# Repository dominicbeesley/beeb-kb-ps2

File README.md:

# beeb-kb-ps2
A BBC Micro Keyboard to PS/2 converter

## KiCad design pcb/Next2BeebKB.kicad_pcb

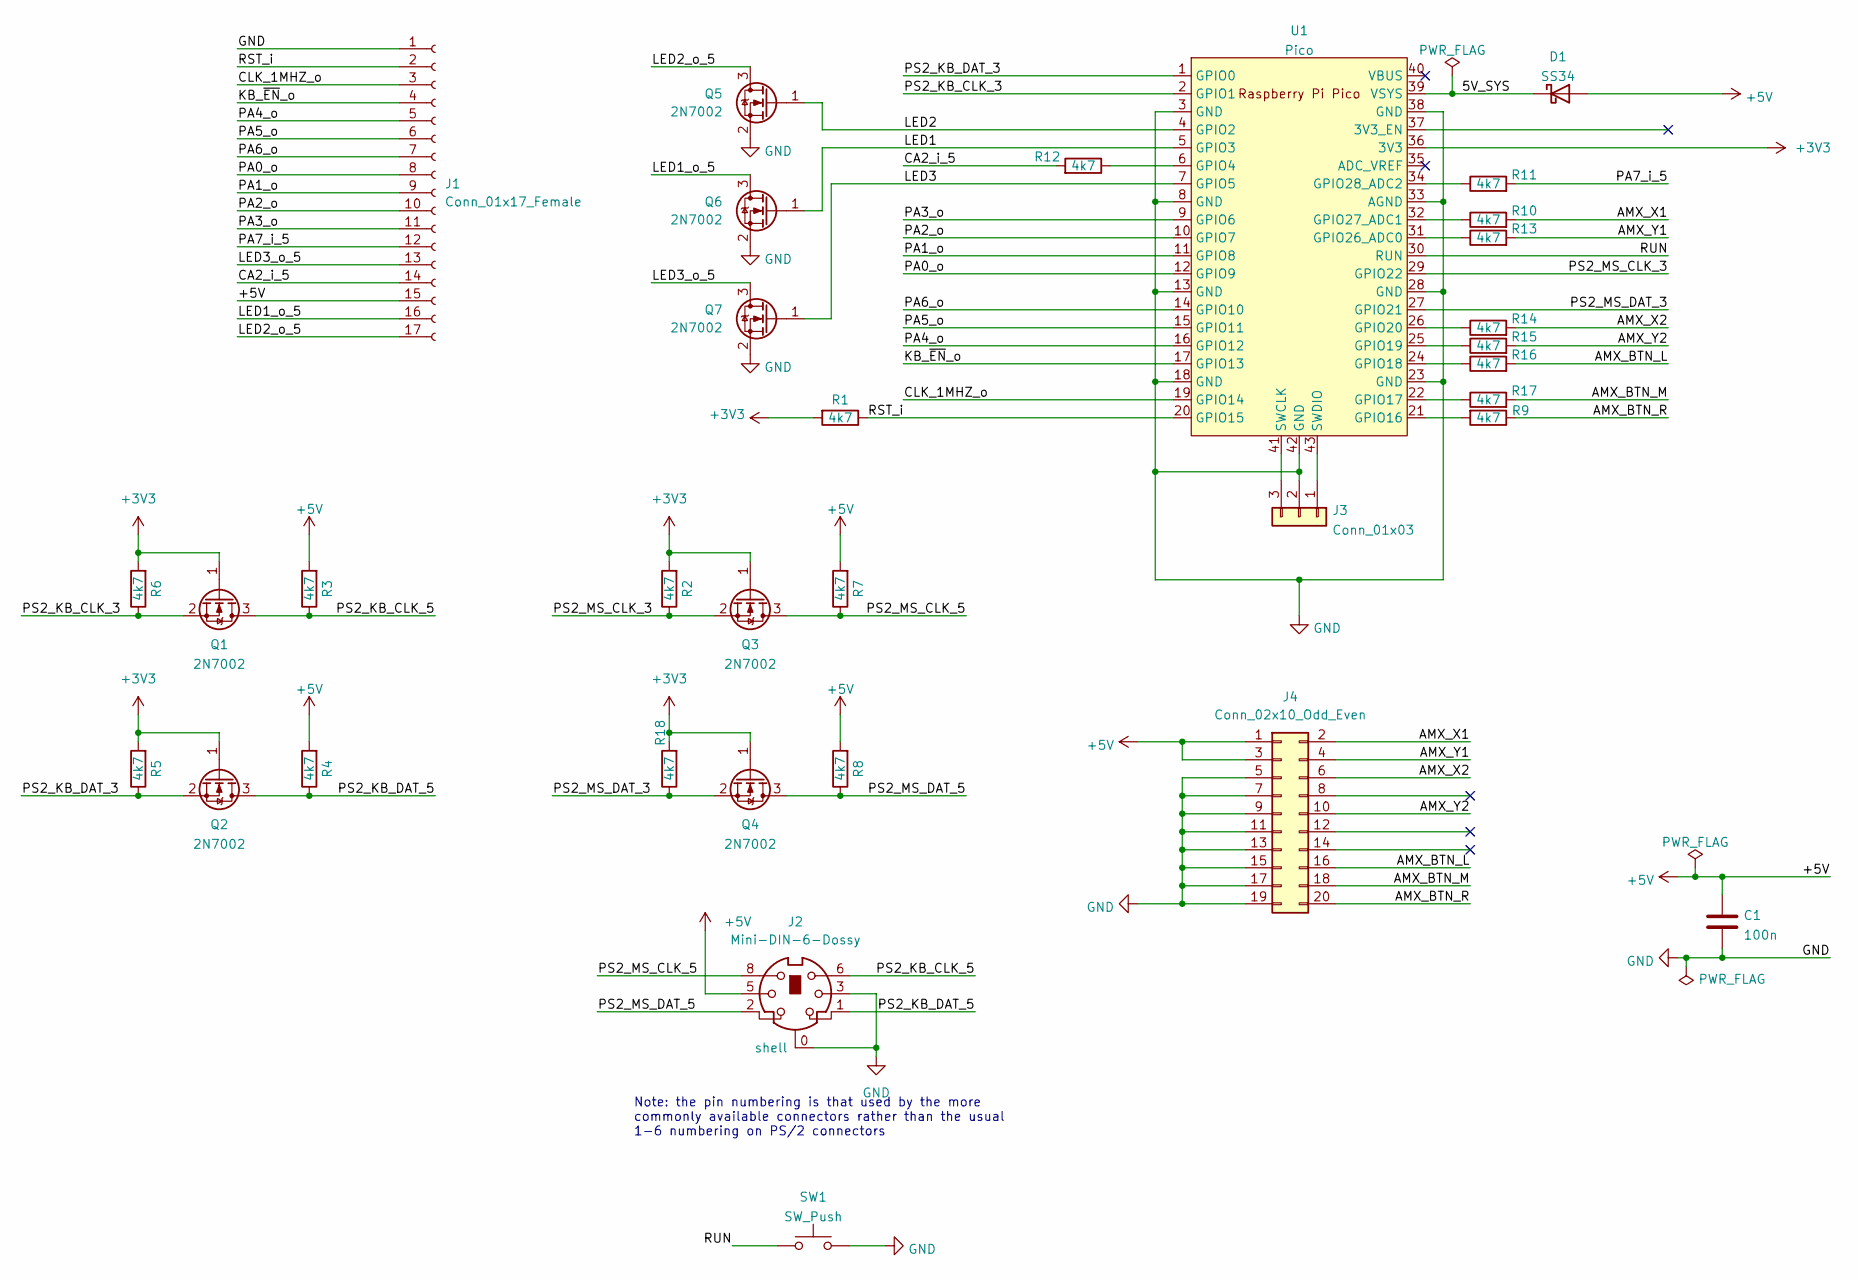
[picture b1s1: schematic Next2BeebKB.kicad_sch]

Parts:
C1: 100n; C_0805_2012Metric; LCSC C49678
D1: SS34; D_SMA; LCSC C8678
J1: Conn_01x17_Female; PinSocket_1x17_P2.54mm_Vertical
J2: Mini-DIN-6-Dossy; PS2 mini din 6
J3: Conn_01x03; PinHeader_1x03_P2.54mm_Vertical
J4: Conn_02x10_Odd_Even; IDC-Header_2x10_P2.54mm_Vertical
Q1, Q2, Q5, Q6, Q7: 2N7002; SOT-23; LCSC C8545
Q3, Q4: 2N7002; SOT-23
R1, R2, R3, R4, R5, R6, R7, R8, R9, R11, R12, R13, R14, R15, R16, R17, R18: 4k7; R_0805_2012Metric; LCSC C17673
R10: 4k7; R_0805_2012Metric
SW1: SW_Push; SW_SPST_GEN
U1: Pico; RPi_Pico_SMD

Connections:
+3V3: Q1.1 (G), Q2.1 (G), Q3.1 (G), Q4.1 (G), R1.2, R2.2, R5.2, R6.2, R18.2, U1.36 (3V3)
+5V: C1.1, D1.2 (A), J1.15, J2.5, J4.1, J4.3, R3.2, R4.2, R7.2, R8.2
/5V_SYS: D1.1 (K), U1.39 (VSYS)
/AMX_BTN_L: J4.16, R16.2
/AMX_BTN_M: J4.18, R17.2
/AMX_BTN_R: J4.20, R9.1
/AMX_X1: J4.2, R10.2
/AMX_X2: J4.6, R14.2
/AMX_Y1: J4.4, R13.2
/AMX_Y2: J4.10, R15.2
/CA2_i_5: J1.14, R12.2
/CLK_1MHZ_o: J1.3, U1.19 (GPIO14)
/KB_~EN_o: J1.4, U1.17 (GPIO13)
/LED1: Q6.1 (G), U1.5 (GPIO3)
/LED1_o_5: J1.16, Q6.3 (D)
/LED2: Q5.1 (G), U1.4 (GPIO2)
/LED2_o_5: J1.17, Q5.3 (D)
/LED3: Q7.1 (G), U1.7 (GPIO5)
/LED3_o_5: J1.13, Q7.3 (D)
/PA0_o: J1.8, U1.12 (GPIO9)
/PA1_o: J1.9, U1.11 (GPIO8)
/PA2_o: J1.10, U1.10 (GPIO7)
/PA3_o: J1.11, U1.9 (GPIO6)
/PA4_o: J1.5, U1.16 (GPIO12)
/PA5_o: J1.6, U1.15 (GPIO11)
/PA6_o: J1.7, U1.14 (GPIO10)
/PA7_i_5: J1.12, R11.2
/PS2_KB_CLK_3: Q1.2 (S), R6.1, U1.2 (GPIO1)
/PS2_KB_CLK_5: J2.6, Q1.3 (D), R3.1
/PS2_KB_DAT_3: Q2.2 (S), R5.1, U1.1 (GPIO0)
/PS2_KB_DAT_5: J2.1, Q2.3 (D), R4.1
/PS2_MS_CLK_3: Q3.2 (S), R2.1, U1.29 (GPIO22)
/PS2_MS_CLK_5: J2.8, Q3.3 (D), R7.1
/PS2_MS_DAT_3: Q4.2 (S), R18.1, U1.27 (GPIO21)
/PS2_MS_DAT_5: J2.2, Q4.3 (D), R8.1
/RST_i: J1.2, R1.1, U1.20 (GPIO15)
/RUN: SW1.1, U1.30 (RUN)
GND: C1.2, J1.1, J2.0 (shell), J2.3, J3.2, J4.5, J4.7, J4.9, J4.11, J4.13, J4.15, J4.17, J4.19, Q5.2 (S), Q6.2 (S), Q7.2 (S), SW1.2, U1.3 (GND), U1.8 (GND), U1.13 (GND), U1.18 (GND), U1.23 (GND), U1.28 (GND), U1.33 (AGND), U1.38 (GND), U1.42 (GND)
unnamed: J3.1, U1.43 (SWDIO)
unnamed: J3.3, U1.41 (SWCLK)
unnamed: R9.2, U1.21 (GPIO16)
unnamed: R10.1, U1.32 (GPIO27_ADC1)
unnamed: R11.1, U1.34 (GPIO28_ADC2)
unnamed: R12.1, U1.6 (GPIO4)
unnamed: R13.1, U1.31 (GPIO26_ADC0)
unnamed: R14.1, U1.26 (GPIO20)
unnamed: R15.1, U1.25 (GPIO19)
unnamed: R16.1, U1.24 (GPIO18)
unnamed: R17.1, U1.22 (GPIO17)

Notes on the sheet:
Note: the pin numbering is that used by the more commonly available connectors rather than the usual 1-6 numbering on PS/2 connectors

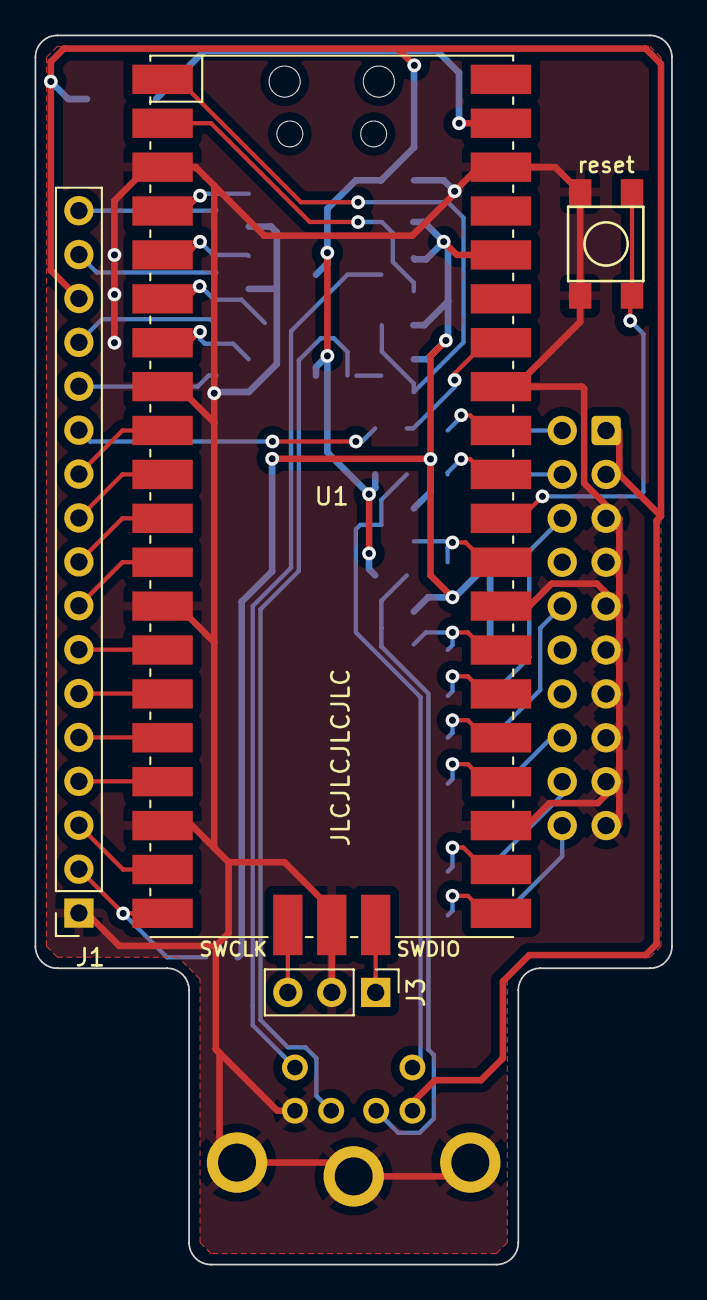
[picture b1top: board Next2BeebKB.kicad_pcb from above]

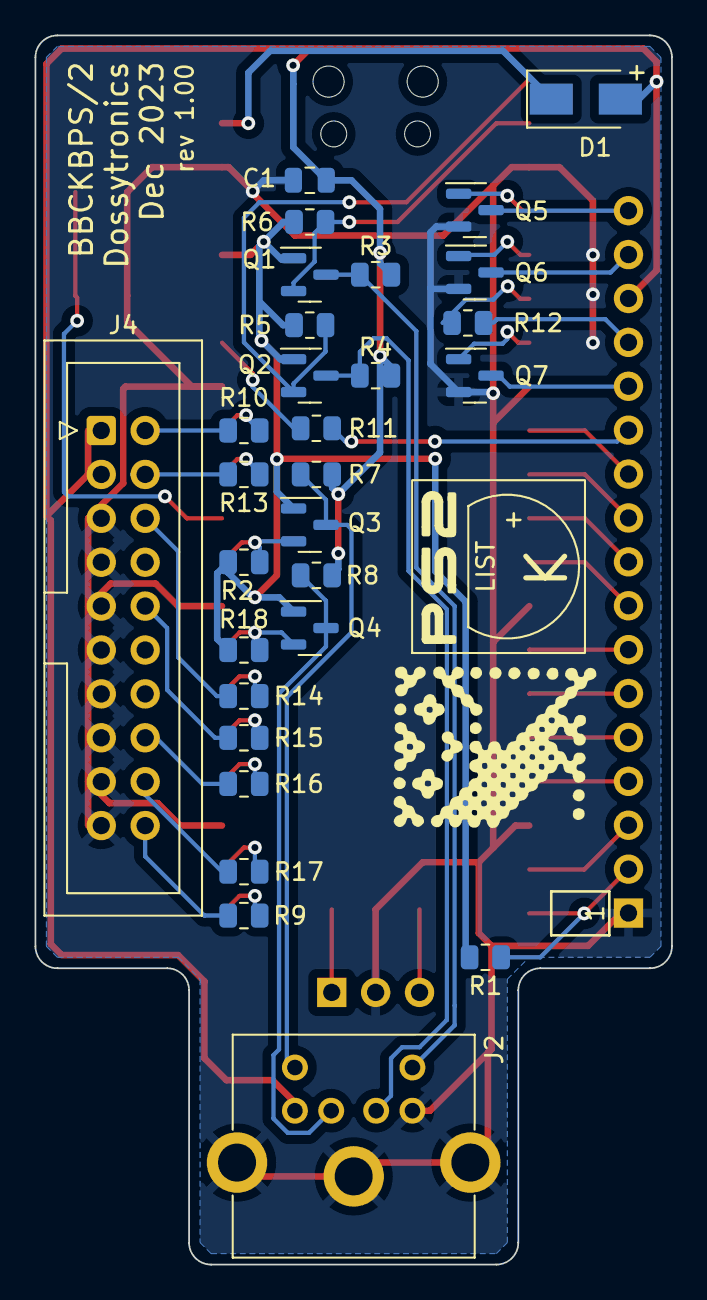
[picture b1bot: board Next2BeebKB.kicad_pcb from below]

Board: 2 copper layers, 36.8 x 71.1 mm, 33 parts (29 on the bottom side), 49 nets.

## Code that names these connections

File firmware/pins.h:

#ifndef __BEEBKEYNEXTPINS_H__
#define __BEEBKEYNEXTPINS_H__

//PS/2 connector - keyboard
#define GPIO_PS2KB_DAT_PIN  0
#define GPIO_PS2KB_CLK_PIN  1
//PS/2 connector - mouse
#define GPIO_PS2MS_DAT_PIN  21
#define GPIO_PS2MS_CLK_PIN  22

//AMX connector
#define GPIO_AMX_BTN_L      18
#define GPIO_AMX_BTN_M      17
#define GPIO_AMX_BTN_R      16
#define GPIO_AMX_X1         27
#define GPIO_AMX_X2         20
#define GPIO_AMX_Y1         26
#define GPIO_AMX_Y2         19


#define GPIO_CA2_IN_PIN     4
#define GPIO_KB_EN_PIN      13
#define GPIO_1MHZ_PIN       14
#define GPIO_PA7_IN_PIN     28

#define GPIO_PA0_OUT_PIN    9
#define GPIO_PA1_OUT_PIN    8
#define GPIO_PA2_OUT_PIN    7
#define GPIO_PA3_OUT_PIN    6
#define GPIO_PA4_OUT_PIN    12
#define GPIO_PA5_OUT_PIN    11
#define GPIO_PA6_OUT_PIN    10

#define GPIO_LED1_PIN       3
#define GPIO_LED2_PIN       2
#define GPIO_LED3_PIN       5

#define GPIO_RST_IN         15

#endif

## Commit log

2024-01-08 1st commit
2024-01-08 repin for updated board
2024-01-10 FIX: host to device communication got stuck
2024-01-10 correct polarity and ordering of LEDs
2024-01-12 mouse wiring
2024-01-12 document conversion of MS/04 mouse
2024-01-12 add amx pins
2024-01-12 swap directions - mdfs.net misleading?
2024-01-12 Swap X
2024-01-12 read mouse with interrupts test
2024-01-13 abstract out ps/2 communication from keyboard specifics
2024-01-13 separate out mouse and keyboard parts
2024-01-13 mouse 1st cut working in 4 byte stream mode
2024-01-13 detect movement on all edges for greater dpi
2024-01-18 separate out mouse and keyboard onto separate cores
2024-01-25 Fixes for protocol not working when inhibited by host
    Still not working with LEDs on PS2/USB
2025-06-05 don't output debug messages
2025-07-10 Add pcb
